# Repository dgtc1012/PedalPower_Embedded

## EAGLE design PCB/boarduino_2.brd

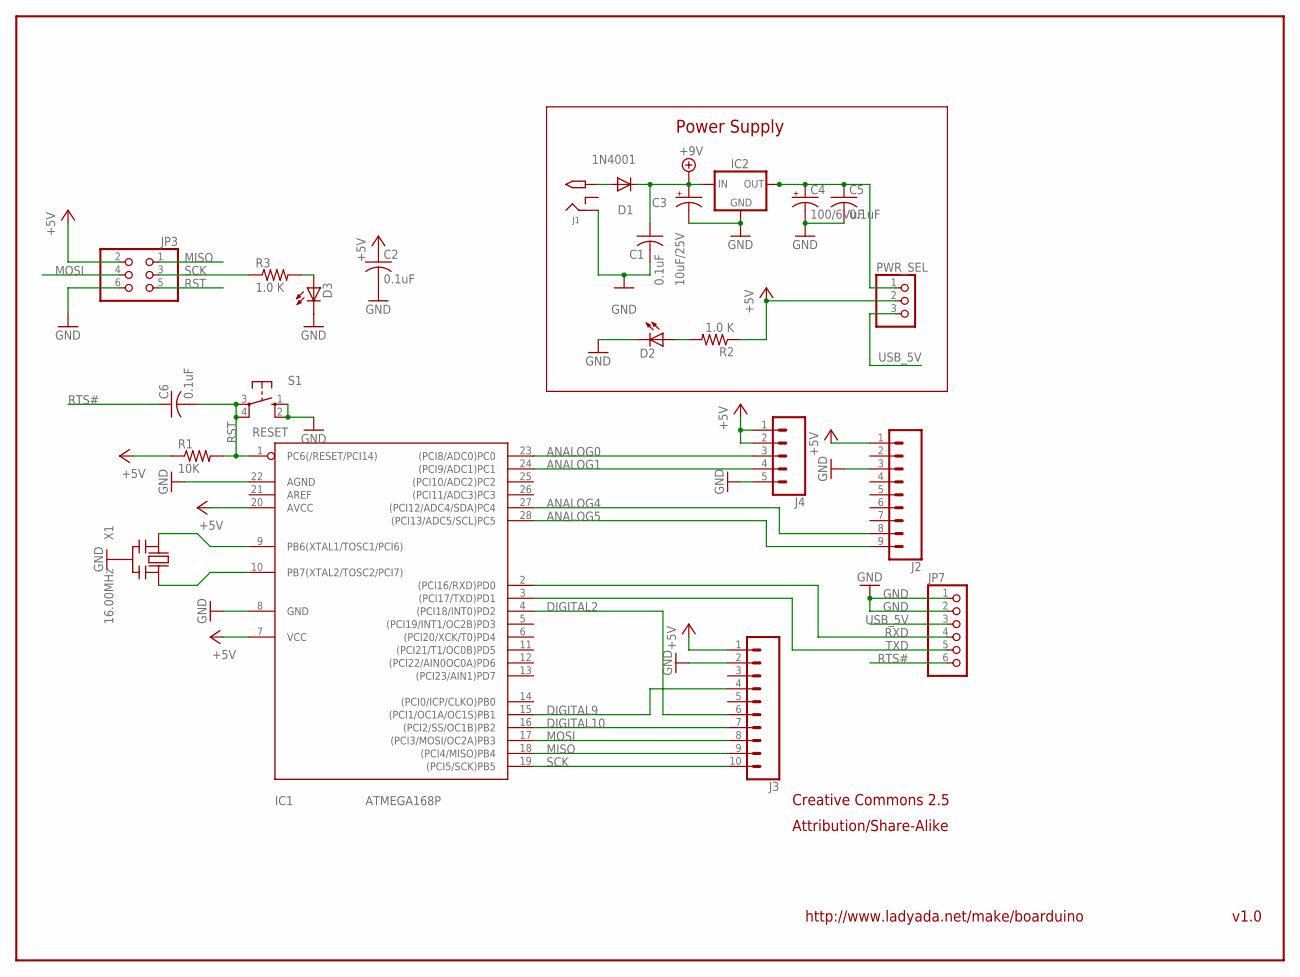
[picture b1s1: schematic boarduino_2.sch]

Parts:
C1, C2, C5, C6: 0.1uF; C025-025X050
C3: 10uF/25V; E2,5-6
C4: 100/6VuF; E2,5-6
D1: 1N4001; DO41-10
D2: LED3MM
D3: Green; LED3MM
IC1: ATMEGA168P; DIL28/3
IC2: 78XXS
J1: 2.1MMJACK; PJ-102A
J2: CONN_09; 1X09
J3: CONN_10"; 1X10
J4: CONN_05; 1X05
JP3: PINHD-2X3; 2X03
JP7: PINHD-1X6CLEAN; 1X06-CLEAN
PWR_SEL: PINHD-1X3; 1X03
R1: 10K; 0207/5V
R2, R3: 1.0 K; 0207/5V
S1: RESET; B3F-10XX
X1: 16.00MHz; CERM_OSC

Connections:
+5V: C2.1, IC1.7 (VCC), IC1.20 (AVCC), J2.1, J3.1, J4.1, J4.2, JP3.2, PWR_SEL.2, R1.1, R2.1
+9V: C1.1, C3.+, D1.C, IC2.IN
ANALOG0: IC1.23 ((PCI8/ADC0)PC0), J4.3
ANALOG1: IC1.24 ((PCI9/ADC1)PC1), J4.4
ANALOG4: IC1.27 ((PCI12/ADC4/SDA)PC4), J2.8
ANALOG5: IC1.28 ((PCI13/ADC5/SCL)PC5), J2.9
DIGITAL2: IC1.4 ((PCI18/INT0)PD2), J3.6
DIGITAL9: IC1.15 ((PCI1/OC1A/OC1S)PB1), J3.4
DIGITAL10: IC1.16 ((PCI2/SS/OC1B)PB2), J3.7
GND: C1.2, C2.2, C3.-, C4.-, C5.2, D2.K (C), D3.K (C), IC1.8 (GND), IC1.22 (AGND), IC2.GND, J1.RING, J2.3, J3.2, J4.5, JP3.6, JP7.1, JP7.2, S1.1 (S), S1.2 (S1), X1.P$2 (GND)
MISO: IC1.18 ((PCI4/MISO)PB4), J3.9, JP3.1
MOSI: IC1.17 ((PCI3/MOSI/OC2A)PB3), J3.8, JP3.4
unnamed: IC1.9 (PB6(XTAL1/TOSC1/PCI6)), X1.P$1 (IN)
unnamed: IC1.10 (PB7(XTAL2/TOSC2/PCI7)), X1.P$3 (OUT)
unnamed: D2.A, R2.2
unnamed: D3.A, R3.2
unnamed: D1.A, J1.TIP
unnamed: C4.+, C5.1, IC2.OUT, PWR_SEL.1
RST: C6.2, IC1.1 (PC6(/RESET/PCI14)), JP3.5, R1.2, S1.3, S1.4 (P1)
RTS#: C6.1, JP7.6
RXD: IC1.2 ((PCI16/RXD)PD0), JP7.4
SCK: IC1.19 ((PCI5/SCK)PB5), J3.10, JP3.3, R3.1
TXD: IC1.3 ((PCI17/TXD)PD1), JP7.5
USB_5V: JP7.3, PWR_SEL.3

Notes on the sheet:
Power Supply
v1.0
http://www.ladyada.net/make/boarduino
Creative Commons 2.5
Attribution/Share-Alike

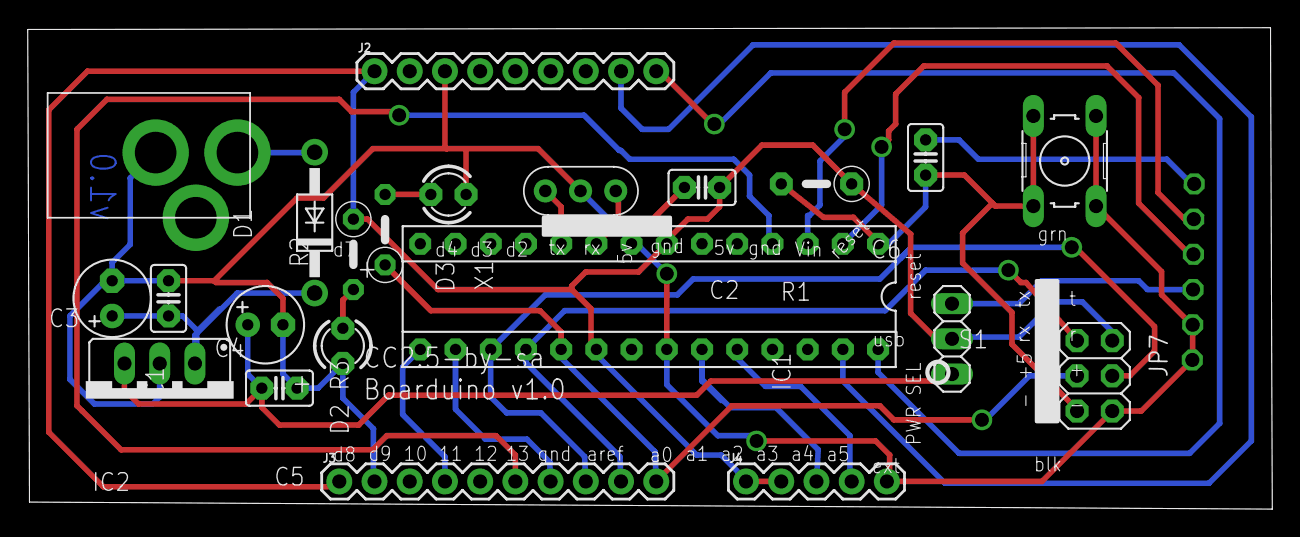
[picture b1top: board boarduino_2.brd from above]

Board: 2 copper layers, 89.8 x 34.7 mm, 23 parts (0 on the bottom side), 24 nets.

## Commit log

2018-03-26 added pcb design and solidworks design files

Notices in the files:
parts and their libraries:
SparkFun-Connectors: Licensing: Creative Commons ShareAlike 4.0 International - https://creativecommons.org/licenses/by-sa/4.0
